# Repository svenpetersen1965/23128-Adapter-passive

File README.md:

# 23128-Adapter-passive
This is an EPROM adapter for Commodore C16 (C254). It also works as a kernal adapter for the C64 (4x BASIC+Kernal). The better option for the C64 can be found <a href="https://github.com/svenpetersen1965/C64-Kernal-Adaptor-Switch-short-board-">here</a>

It allows up to 4 Kernals for the C16, which can be selected by jumpers.

BOM value (12.12.2020): 3.81€

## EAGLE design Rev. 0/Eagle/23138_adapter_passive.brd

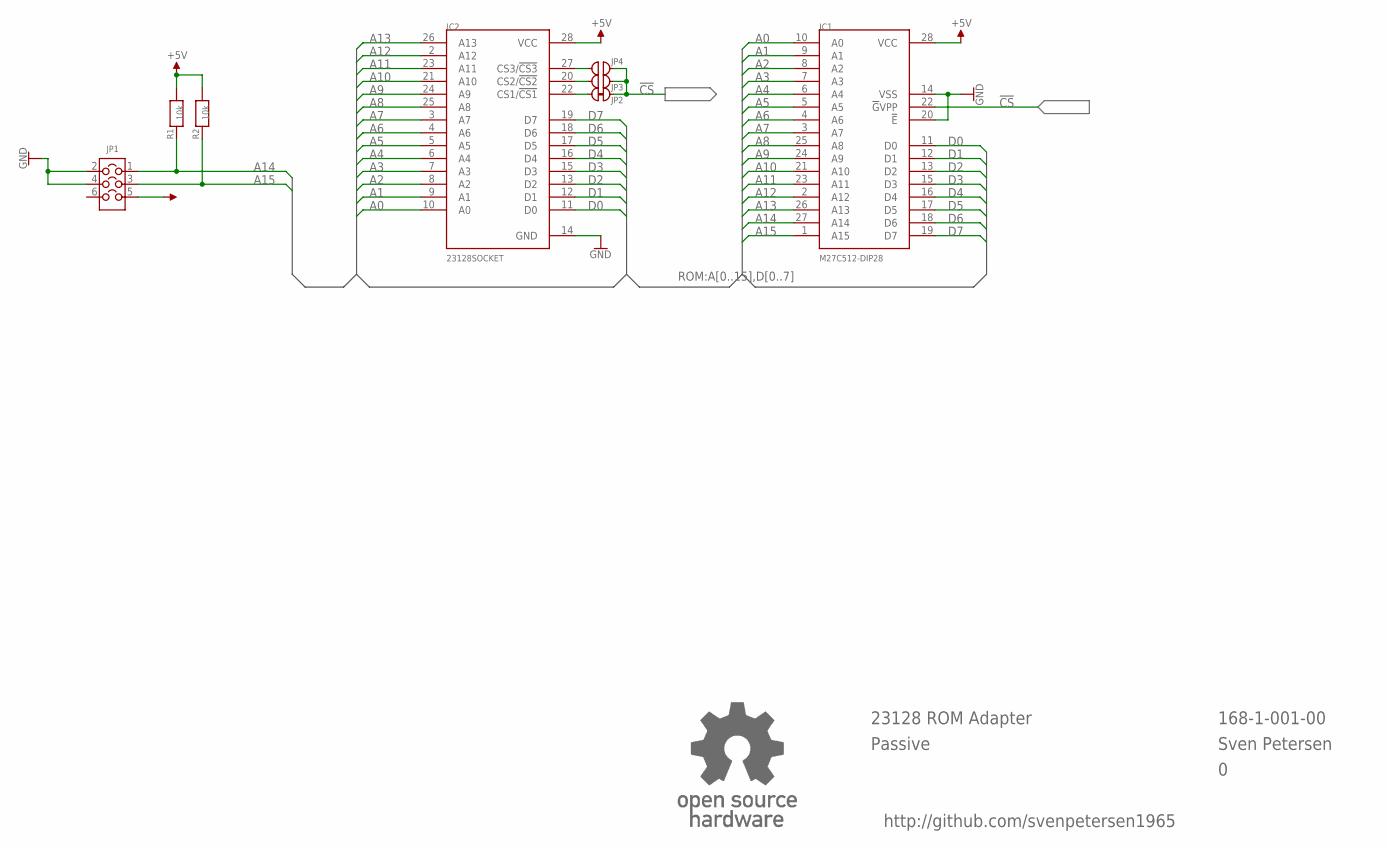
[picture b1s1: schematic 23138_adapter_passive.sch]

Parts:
IC1: M27C512-DIP28; DIL28-6
IC2: 23128SOCKET; DIL28_SOCKET
JP1: COMBI-3X2P-90°; COMBI-3X2W
JP2: CLOSED; CP_CL
JP3, JP4: OPEN; CP_OP
R1, R2: 10k; 0805
U$21: OPEN_SOURCE_HW; OPENHW

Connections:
!CS: IC1.22 (!G!VPP), JP2.2, JP3.2, JP4.2
+5V: IC1.28 (VCC), IC2.28 (VCC), JP1.5, R1.2, R2.2
A0: IC1.10 (A0), IC2.10 (A0)
A1: IC1.9 (A1), IC2.9 (A1)
A2: IC1.8 (A2), IC2.8 (A2)
A3: IC1.7 (A3), IC2.7 (A3)
A4: IC1.6 (A4), IC2.6 (A4)
A5: IC1.5 (A5), IC2.5 (A5)
A6: IC1.4 (A6), IC2.4 (A6)
A7: IC1.3 (A7), IC2.3 (A7)
A8: IC1.25 (A8), IC2.25 (A8)
A9: IC1.24 (A9), IC2.24 (A9)
A10: IC1.21 (A10), IC2.21 (A10)
A11: IC1.23 (A11), IC2.23 (A11)
A12: IC1.2 (A12), IC2.2 (A12)
A13: IC1.26 (A13), IC2.26 (A13)
A14: IC1.27 (A14), JP1.1, R1.1
A15: IC1.1 (A15), JP1.3, R2.1
D0: IC1.11 (D0), IC2.11 (D0)
D1: IC1.12 (D1), IC2.12 (D1)
D2: IC1.13 (D2), IC2.13 (D2)
D3: IC1.15 (D3), IC2.15 (D3)
D4: IC1.16 (D4), IC2.16 (D4)
D5: IC1.17 (D5), IC2.17 (D5)
D6: IC1.18 (D6), IC2.18 (D6)
D7: IC1.19 (D7), IC2.19 (D7)
GND: IC1.14 (VSS), IC1.20 (!E), IC2.14 (GND), JP1.2, JP1.4
unnamed: IC2.22 (CS1/!CS1), JP2.1
unnamed: IC2.27 (CS3/!CS3), JP4.1
unnamed: IC2.20 (CS2/!CS2), JP3.1

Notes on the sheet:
168-1-001-00
Sven Petersen
23128 ROM Adapter
Passive
http://github.com/svenpetersen1965

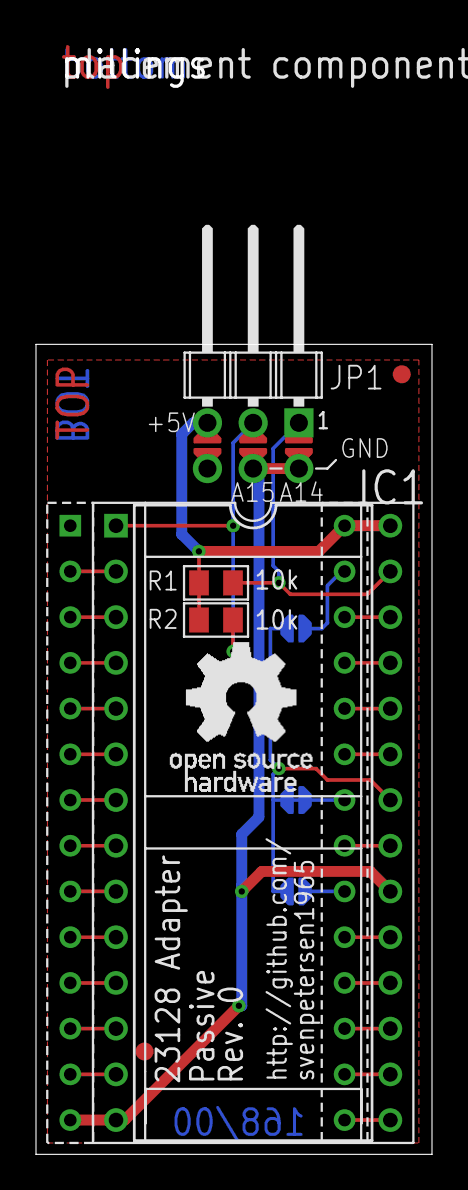
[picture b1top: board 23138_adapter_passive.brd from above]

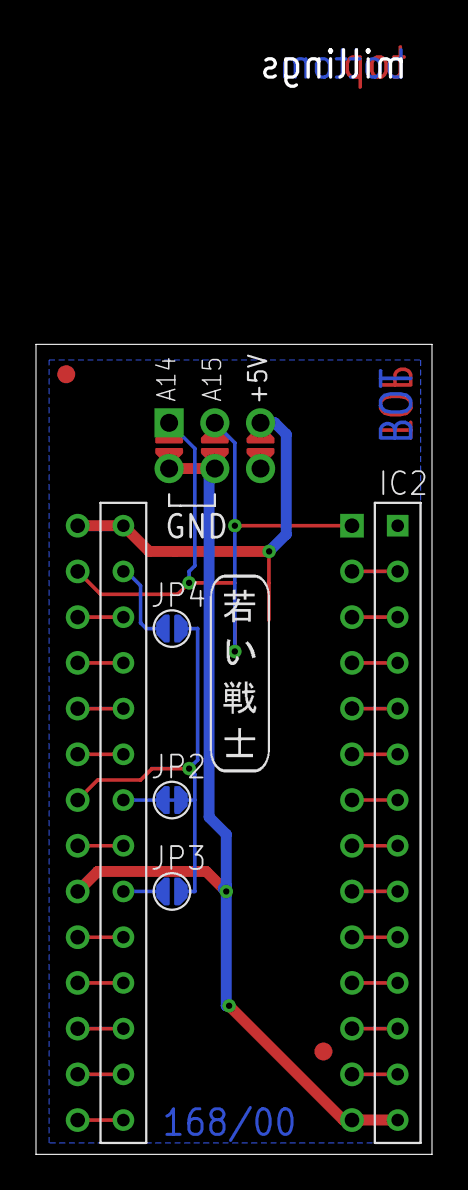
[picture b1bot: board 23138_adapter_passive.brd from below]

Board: 2 copper layers, 22.0 x 45.0 mm, 15 parts (4 on the bottom side), 30 nets.

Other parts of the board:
U$16: GS28P
U$17, U$18: SMD_REF_R1MM
U$19: 2LAYER
U$20: PCB-TITLE/
U$22: SVEN_TAG

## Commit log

2020-12-12 Added calculation
